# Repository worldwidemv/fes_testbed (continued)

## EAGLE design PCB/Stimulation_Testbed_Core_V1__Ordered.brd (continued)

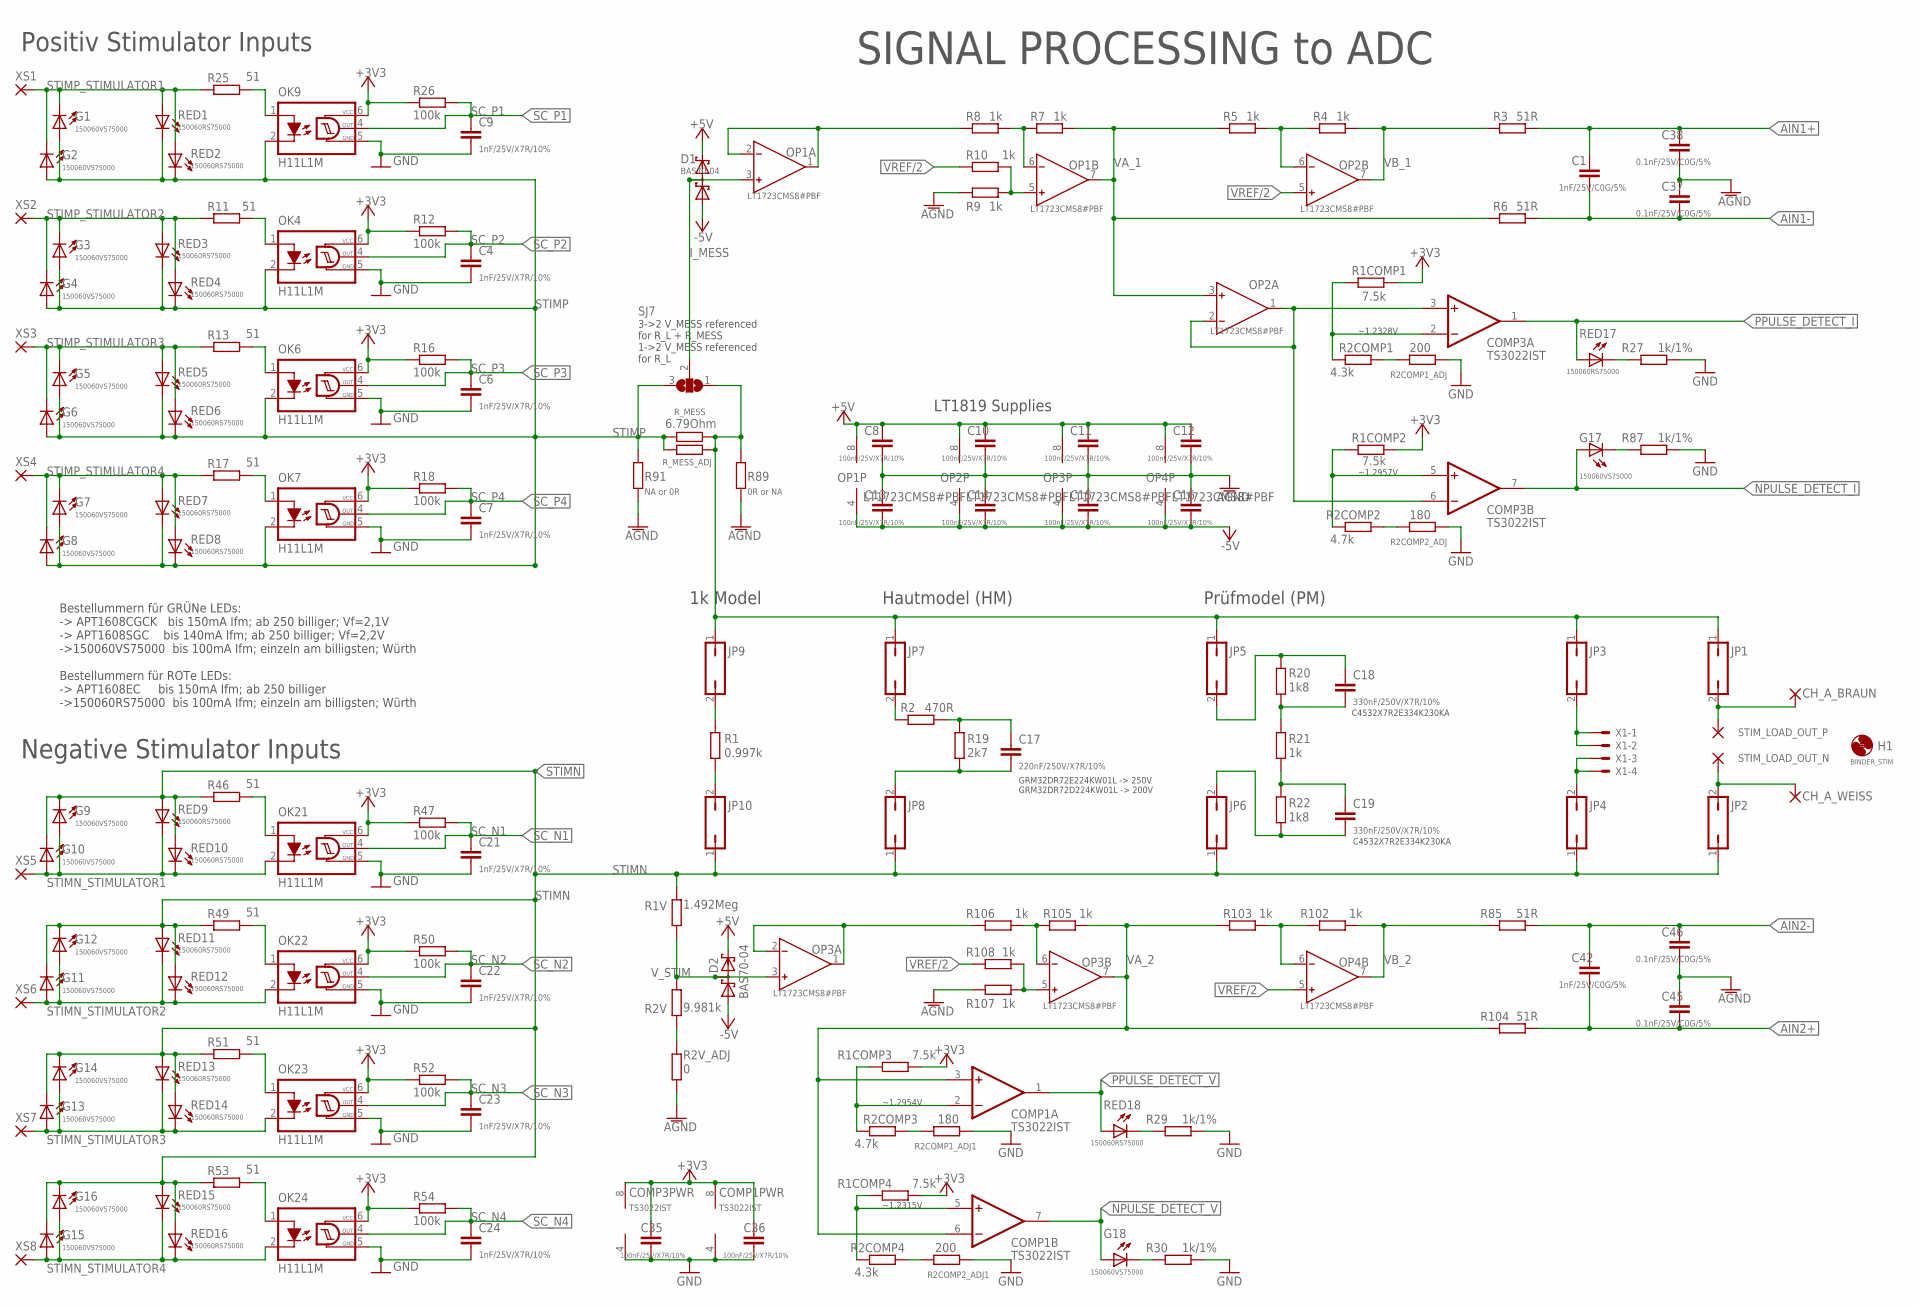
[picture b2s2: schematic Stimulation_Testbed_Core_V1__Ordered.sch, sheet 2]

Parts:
C1, C42: 1nF/25V/C0G/5%; C0603K
C4, C6, C7, C9, C21, C22, C23, C24: 1nF/25V/X7R/10%; C0603
C8, C10, C11, C12, C13, C14, C15, C16, C35, C36: 100nF/25V/X7R/10%; C0603K
C17: 220nF/250V/X7R/10%; C1210
C18, C19: 330nF/250V/X7R/10%; C1812
C37, C38, C45, C46: 0.1nF/25V/C0G/5%; C0603K
CH_A_BRAUN: 1,6/0,8
CH_A_WEISS: 1,6/0,8
COMP1, COMP3: TS3022IST; MSOP8
D1, D2: BAS70-04; SOT23
G1, G2, G3, G4, G5, G6, G7, G8, G9, G10, G11, G12, G13, G14, G15, G16, G17, G18: 150060VS75000; CHIPLED_0603
H1: BINDER_STIM; 5,5-PAD
JP1, JP2, JP3, JP4, JP5, JP6, JP7, JP8, JP9, JP10: JP1Q; JP1
OK4, OK6, OK7, OK9, OK21, OK22, OK23, OK24: H11L1M; DIL06
OP1, OP2, OP3, OP4: LT1723CMS8#PBF; MSOP8
R1: 0.997k; R1206
R1COMP1, R1COMP2, R1COMP3, R1COMP4: 7.5k; R0603
R1V: 1.492Meg; R1206
R2: 470R; R1206
R2COMP1, R2COMP4: 4.3k; R0603
R2COMP1_ADJ, R2COMP2_ADJ1: 200; R0603
R2COMP1_ADJ1, R2COMP2_ADJ: 180; R0603
R2COMP2, R2COMP3: 4.7k; R0603
R2V: 9.981k; R1206
R2V_ADJ: 0; R1206
R3, R6, R85, R104: 51R; R0603
R4, R5, R7, R8, R9, R10, R102, R103, R105, R106, R107, R108: 1k; R0603
R11, R13, R17, R25, R46, R49, R51, R53: 51; R0603
R12, R16, R18, R26, R47, R50, R52, R54: 100k; R0603
R19: 2k7; R1206
R20, R22: 1k8; R1206
R21: 1k; R1206
R27, R29, R30, R87: 1k/1%; R0603
R89: 0R or NA; R0603
R91: NA or 0R; R0603
RED1, RED2, RED3, RED4, RED5, RED6, RED7, RED8, RED9, RED10, RED11, RED12, RED13, RED14, RED15, RED16, RED17, RED18: 150060RS75000; CHIP-LED0603
R_MESS: 6.79Ohm; R1206
R_MESS_ADJ: R-EU_R1206; R1206
SJ7: SJ2W; SJ_2
STIM_LOAD_OUT_N: 3,81/1,4
STIM_LOAD_OUT_P: 3,81/1,4
X1: 22-23-2041
XS1, XS2, XS3, XS4, XS5, XS6, XS7, XS8: WIREPAD3,81/1,4; 3,81/1,4

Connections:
2XVREF: OP3.1 (OUT), OP3.2 (IN-), R106.2
2XVREF1: OP1.1 (OUT), OP1.2 (IN-), R8.2
+3V3: C35.1, C36.1, COMP1.8 (V+), COMP3.8 (V+), OK4.6 (VCC), OK6.6 (VCC), OK7.6 (VCC), OK9.6 (VCC), OK21.6 (VCC), OK22.6 (VCC), OK23.6 (VCC), OK24.6 (VCC), R1COMP1.1, R1COMP2.1, R1COMP3.1, R1COMP4.1, R12.1, R16.1, R18.1, R26.1, R47.1, R50.1, R52.1, R54.1; also elsewhere on the board
+5V: C8.1, C10.1, C11.1, C12.1, D1.2 (C2), D2.2 (C2), OP1.8 (V+), OP2.8 (V+), OP3.8 (V+), OP4.8 (V+); also elsewhere on the board
-5V: C13.2, C14.2, C15.2, C16.2, D1.1 (A1), D2.1 (A1), OP1.4 (V-), OP2.4 (V-), OP3.4 (V-), OP4.4 (V-); also elsewhere on the board
AGND: C8.2, C10.2, C11.2, C12.2, C13.1, C14.1, C15.1, C16.1, C37.2, C38.1, C45.2, C46.1, R2V_ADJ.2, R9.2, R89.2, R91.2, R107.2; also elsewhere on the board
AIN1+: C1.2, C38.2, R3.1; also elsewhere on the board
AIN1-: C1.1, C37.1, R6.2; also elsewhere on the board
AIN2+: C42.1, C45.1, R104.2; also elsewhere on the board
AIN2-: C42.2, C46.2, R85.1; also elsewhere on the board
GND: C4.2, C6.2, C7.2, C9.2, C21.2, C22.2, C23.2, C24.2, C35.2, C36.2, COMP1.4 (V-), COMP3.4 (V-), OK4.5 (GND), OK6.5 (GND), OK7.5 (GND), OK9.5 (GND), OK21.5 (GND), OK22.5 (GND), OK23.5 (GND), OK24.5 (GND), R2COMP1_ADJ.1, R2COMP1_ADJ1.1, R2COMP2_ADJ.1, R2COMP2_ADJ1.1, R27.1, R29.1, R30.1, R87.1; also elsewhere on the board
I_MESS: D1.3 (C1A2), OP1.3 (IN+), SJ7.2
unnamed: OK4.1 (A), R11.1
unnamed: R2COMP2.2, R2COMP2_ADJ.2
unnamed: R29.2, RED18.C
unnamed: G18.C, R30.2
unnamed: COMP1.2 (-IN), R1COMP3.2, R2COMP3.1
unnamed: COMP1.5 (+IN), R1COMP4.2, R2COMP4.1
unnamed: G17.C, R87.2
unnamed: OP1.5 (IN+), R9.1, R10.1
unnamed: R2COMP1_ADJ1.2, R2COMP3.2
unnamed: R2COMP2_ADJ1.2, R2COMP4.2
unnamed: OK6.1 (A), R13.1
unnamed: OK7.1 (A), R17.1
unnamed: OK9.1 (A), R25.1
unnamed: OP1.6 (IN-), R7.2, R8.1
unnamed: OP2.6 (IN-), R4.2, R5.1
unnamed: COMP3.3 (+IN), COMP3.6 (-IN), OP2.1 (OUT), OP2.2 (IN-)
unnamed: OK21.1 (A), R46.1
unnamed: COMP3.2 (-IN), R1COMP1.2, R2COMP1.1
unnamed: CH_A_WEISS.1, JP2.2, STIM_LOAD_OUT_N.1
unnamed: OK22.1 (A), R49.1
unnamed: OK23.1 (A), R51.1
unnamed: OK24.1 (A), R53.1
unnamed: R2V.1, R2V_ADJ.1
unnamed: OP3.5 (IN+), R107.1, R108.1
unnamed: CH_A_BRAUN.1, JP1.2, STIM_LOAD_OUT_P.1
unnamed: JP3.2, X1.1, X1.2
unnamed: JP9.2, R1.1
unnamed: JP4.2, X1.3, X1.4
unnamed: JP10.2, R1.2
unnamed: JP7.2, R2.2
unnamed: OP3.6 (IN-), R105.2, R106.1
unnamed: C17.1, JP8.2, R19.2
unnamed: C19.2, R21.2, R22.1
unnamed: C19.1, JP6.2, R22.2
unnamed: C18.2, JP5.2, R20.1
unnamed: C18.1, R20.2, R21.1
unnamed: OP4.6 (IN-), R102.2, R103.1
unnamed: C17.2, R2.1, R19.1
unnamed: R27.2, RED17.C
unnamed: COMP3.5 (+IN), R1COMP2.2, R2COMP2.1
unnamed: R2COMP1.2, R2COMP1_ADJ.2
NPULSE_DETECT_I: COMP3.7 (OUT), G17.A; also elsewhere on the board
NPULSE_DETECT_V: COMP1.7 (OUT), G18.A; also elsewhere on the board
PPULSE_DETECT_I: COMP3.1 (OUT), RED17.A; also elsewhere on the board
PPULSE_DETECT_V: COMP1.1 (OUT), RED18.A; also elsewhere on the board
SC_N1: C21.1, OK21.4 (OUT), R47.2; also elsewhere on the board
SC_N2: C22.1, OK22.4 (OUT), R50.2; also elsewhere on the board
SC_N3: C23.1, OK23.4 (OUT), R52.2; also elsewhere on the board
SC_N4: C24.1, OK24.4 (OUT), R54.2; also elsewhere on the board
SC_P1: C9.1, OK9.4 (OUT), R26.2; also elsewhere on the board
SC_P2: C4.1, OK4.4 (OUT), R12.2; also elsewhere on the board
SC_P3: C6.1, OK6.4 (OUT), R16.2; also elsewhere on the board
SC_P4: C7.1, OK7.4 (OUT), R18.2; also elsewhere on the board
STIMN: G9.C, G10.C, G11.C, G12.C, G13.C, G14.C, G15.C, G16.C, JP2.1, JP4.1, JP6.1, JP8.1, JP10.1, R1V.2, R46.2, R49.2, R51.2, R53.2, RED9.A, RED10.A, RED11.A, RED12.A, RED13.A, RED14.A, RED15.A, RED16.A; also elsewhere on the board
STIMN_STIMULATOR1: G9.A, G10.A, OK21.2 (C), RED9.C, RED10.C, XS5.1
STIMN_STIMULATOR2: G11.A, G12.A, OK22.2 (C), RED11.C, RED12.C, XS6.1
STIMN_STIMULATOR3: G13.A, G14.A, OK23.2 (C), RED13.C, RED14.C, XS7.1
STIMN_STIMULATOR4: G15.A, G16.A, OK24.2 (C), RED15.C, RED16.C, XS8.1
STIMP: G1.A, G2.A, G3.A, G4.A, G5.A, G6.A, G7.A, G8.A, OK4.2 (C), OK6.2 (C), OK7.2 (C), OK9.2 (C), R91.1, RED1.C, RED2.C, RED3.C, RED4.C, RED5.C, RED6.C, RED7.C, RED8.C, R_MESS.2, R_MESS_ADJ.1, SJ7.3; also elsewhere on the board
STIMP_MODEL: JP1.1, JP3.1, JP5.1, JP7.1, JP9.1, R89.1, R_MESS.1, R_MESS_ADJ.2, SJ7.1
STIMP_STIMULATOR1: G1.C, G2.C, R25.2, RED1.A, RED2.A, XS1.1
STIMP_STIMULATOR2: G3.C, G4.C, R11.2, RED3.A, RED4.A, XS2.1
STIMP_STIMULATOR3: G5.C, G6.C, R13.2, RED5.A, RED6.A, XS3.1
STIMP_STIMULATOR4: G7.C, G8.C, R17.2, RED7.A, RED8.A, XS4.1
VA_1: OP1.7 (OUT), OP2.3 (IN+), R5.2, R6.1, R7.1
VA_2: COMP1.3 (+IN), COMP1.6 (-IN), OP3.7 (OUT), R103.2, R104.1, R105.1
VB_1: OP2.7 (OUT), R3.2, R4.1
VB_2: OP4.7 (OUT), R85.2, R102.1
VREF/2: OP2.5 (IN+), OP4.5 (IN+), R10.2, R108.2; also elsewhere on the board
V_STIM: D2.3 (C1A2), OP3.3 (IN+), R1V.1, R2V.2

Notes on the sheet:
LT1819 Supplies
1k Model
Hautmodel (HM)
Prüfmodel (PM)
SIGNAL PROCESSING to ADC
3->2 V_MESS referenced for R_L + R_MESS 1->2 V_MESS referenced for R_L
Positiv Stimulator Inputs
Negative Stimulator Inputs
C4532X7R2E334K230KA
GRM32DR72E224KW01L -> 250V GRM32DR72D224KW01L -> 200V
Bestellummern für GRÜNe LEDs: -> APT1608CGCK bis 150mA Ifm; ab 250 billiger; Vf=2,1V -> APT1608SGC bis 140mA Ifm; ab 250 billiger; Vf=2,2V ->150060VS75000 bis 100mA Ifm; einzeln am billigsten; Würth Bestellummern für ROTe LEDs: -> APT1608EC bis 150mA Ifm; ab 250 billiger ->150060RS75000 bis 100mA I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
~1.2328V
~1.2957V
~1.2954V
~1.2315V

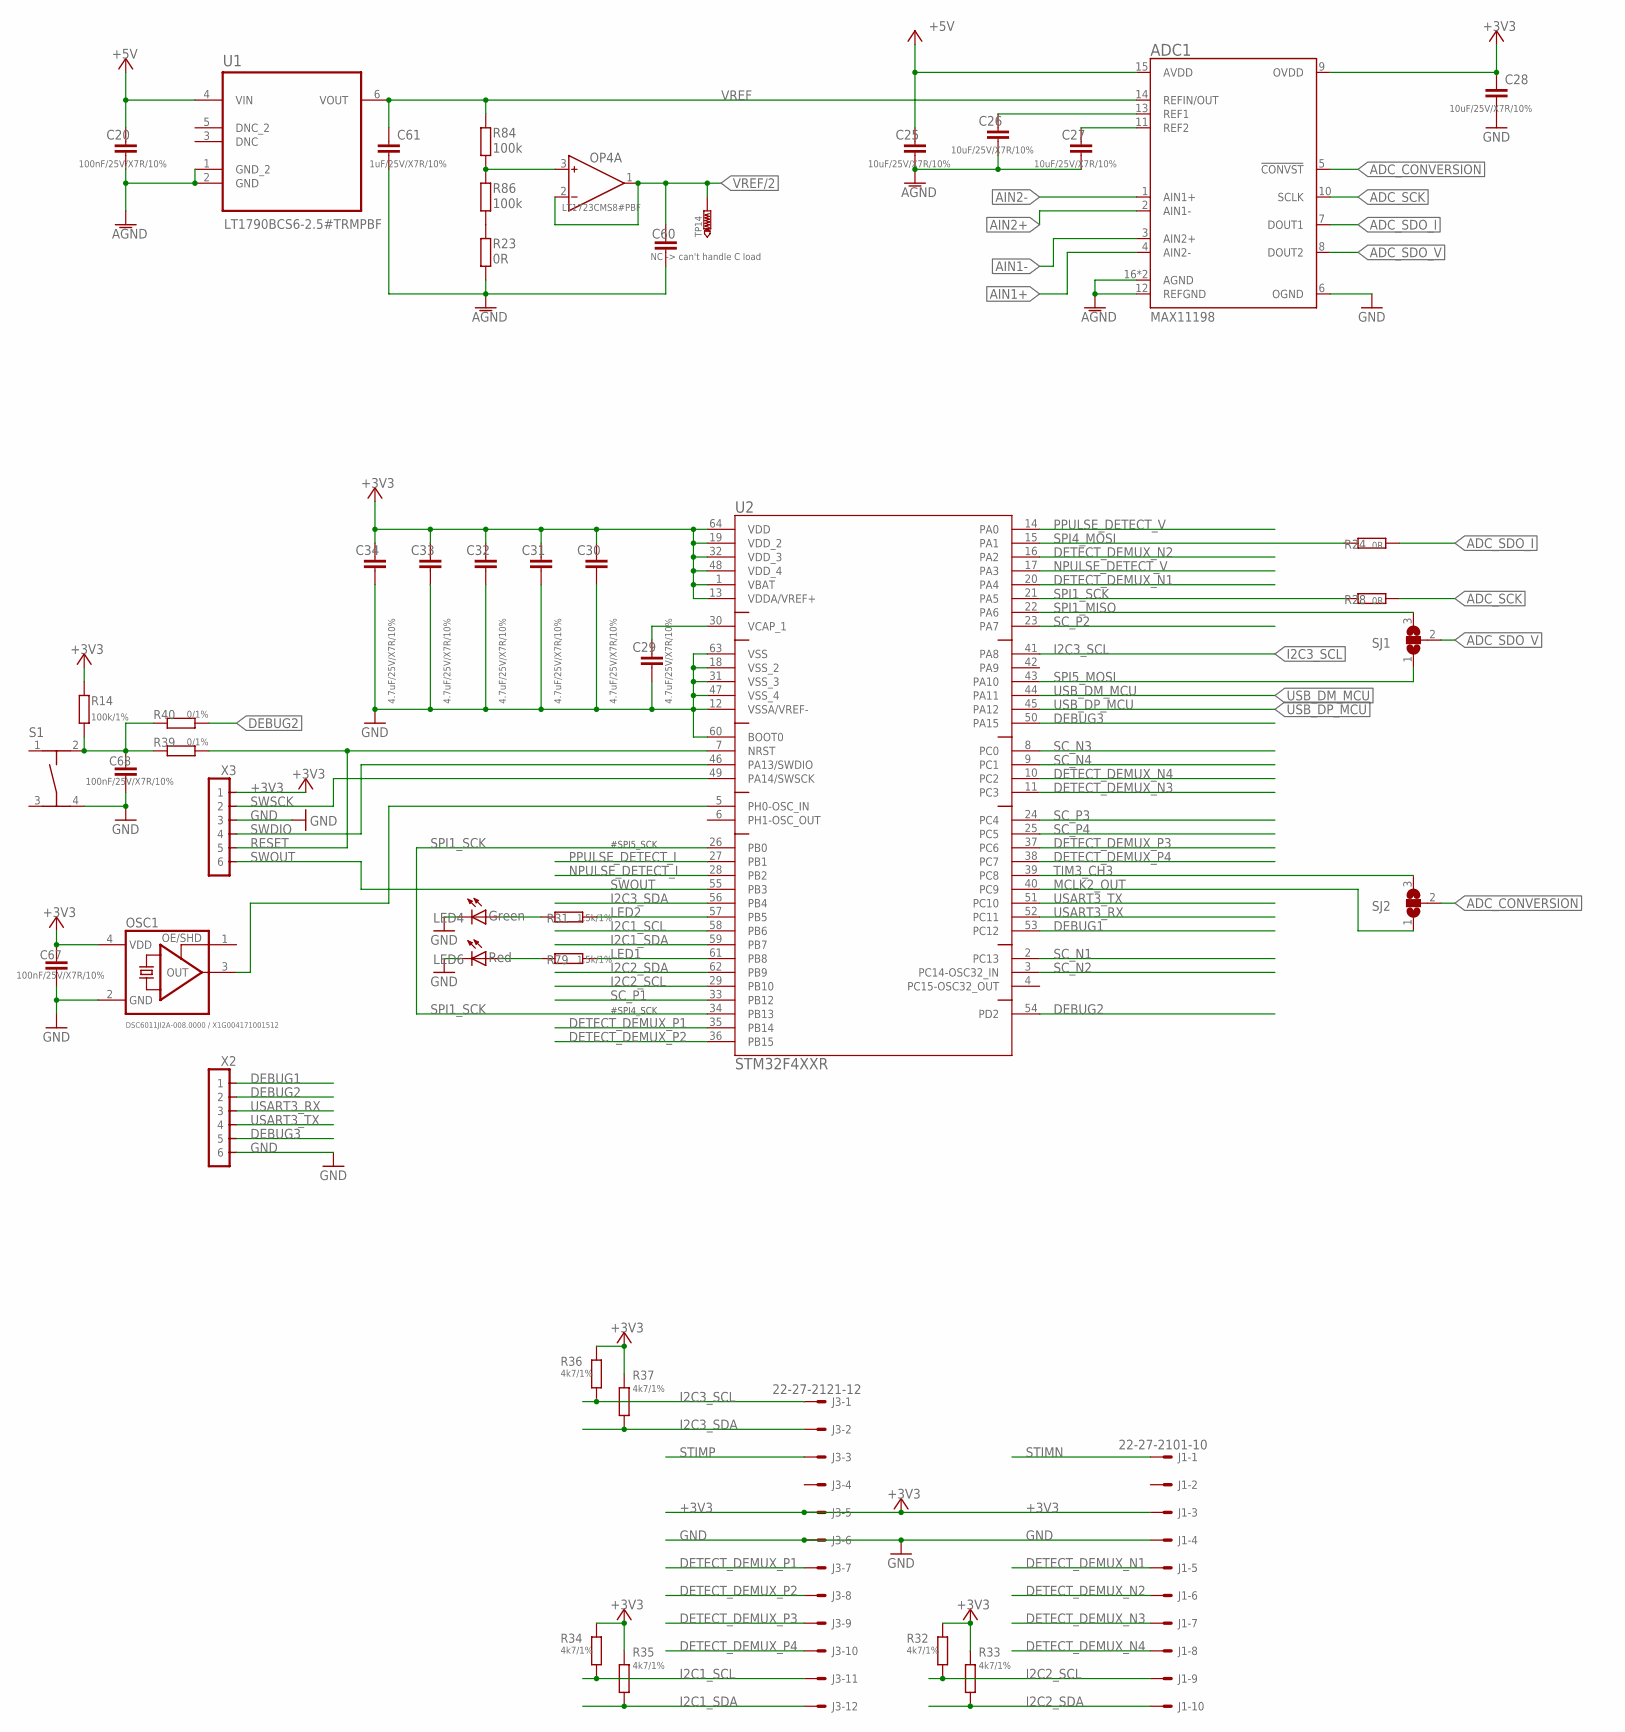
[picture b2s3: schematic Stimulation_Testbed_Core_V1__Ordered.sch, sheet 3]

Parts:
ADC1: MAX11198; T1623CN+1
C20, C67, C68: 100nF/25V/X7R/10%; C0603K
C25, C26, C27, C28: 10uF/25V/X7R/10%; C0603K
C29, C30, C31, C32, C33, C34: 4.7uF/25V/X7R/10%; C0603K
C60: NC -> can't handle C load; C0603K
C61: 1uF/25V/X7R/10%; C0603K
J1: 22-27-2101-10; 6410-10
J3: 22-27-2121-12; 6410-12
LED4: Green; CHIPLED_0603
LED6: Red; CHIPLED_0603
OP4: LT1723CMS8#PBF; MSOP8
OSC1: DSC6011JI2A-008.0000 / X1G004171001512; OSC_2.5X2
R14: 100k/1%; R0603
R23, R24, R28: 0R; R0603
R31, R79: 1.5k/1%; R0603
R32, R33, R34, R35, R36, R37: 4k7/1%; R0603
R39, R40: 0/1%; R0603
R84, R86: 100k; R0603
S1: TASTERSMD; TAST_SMD
SJ1, SJ2: SJ2W; SJ_2
TP14: TESTPOINT_TH; TP1-09
U1: LT1790BCS6-2.5#TRMPBF; SOT95P280X100-6N
U2: STM32F4XXR; LQFP64-10X10MM
X2, X3: PINHD-1X66X1.27; 1.27_1X06_S

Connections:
+3V3: ADC1.9 (OVDD), C28.1, C30.1, C31.1, C32.1, C33.1, C34.1, C67.1, J1.3, J3.5, OSC1.4 (VDD), R14.2, R32.1, R33.1, R34.1, R35.1, R36.1, R37.1, U2.1 (VBAT), U2.13 (VDDA/VREF+), U2.19 (VDD_2), U2.32 (VDD_3), U2.48 (VDD_4), U2.64 (VDD), X3.P1 (1); also elsewhere on the board
+5V: ADC1.15 (AVDD), C20.1, C25.1, U1.4 (VIN); also elsewhere on the board
ADC_CONVERSION: ADC1.5 (!CONVST!), SJ2.2
ADC_SCK: ADC1.10 (SCLK), R28.2
ADC_SDO_I: ADC1.7 (DOUT1), R24.2
ADC_SDO_V: ADC1.8 (DOUT2), SJ1.2
AGND: ADC1.12 (REFGND), ADC1.16 (AGND), ADC1.EXP (AGND), C20.2, C25.2, C26.2, C27.2, C60.2, C61.2, R23.2, U1.1 (GND_2), U1.2 (GND); also elsewhere on the board
AIN1+: ADC1.4 (AIN2-); also elsewhere on the board
AIN1-: ADC1.3 (AIN2+); also elsewhere on the board
AIN2+: ADC1.2 (AIN1-); also elsewhere on the board
AIN2-: ADC1.1 (AIN1+); also elsewhere on the board
DEBUG1: U2.53 (PC12), X2.P1 (1)
DEBUG2: R40.1, U2.54 (PD2), X2.P2 (2)
DEBUG3: U2.50 (PA15), X2.P5 (5)
DETECT_DEMUX_N1: J1.5, U2.20 (PA4)
DETECT_DEMUX_N2: J1.6, U2.16 (PA2)
DETECT_DEMUX_N3: J1.7, U2.11 (PC3)
DETECT_DEMUX_N4: J1.8, U2.10 (PC2)
DETECT_DEMUX_P1: J3.7, U2.35 (PB14)
DETECT_DEMUX_P2: J3.8, U2.36 (PB15)
DETECT_DEMUX_P3: J3.9, U2.37 (PC6)
DETECT_DEMUX_P4: J3.10, U2.38 (PC7)
GND: ADC1.6 (OGND), C28.2, C29.2, C30.2, C31.2, C32.2, C33.2, C34.2, C67.2, C68.2, J1.4, J3.6, LED4.C, LED6.C, OSC1.2 (GND), S1.4, U2.12 (VSSA/VREF-), U2.18 (VSS_2), U2.31 (VSS_3), U2.47 (VSS_4), U2.60 (BOOT0), U2.63 (VSS), X2.P6 (6), X3.P3 (3); also elsewhere on the board
I2C1_SCL: J3.11, R34.2, U2.58 (PB6)
I2C1_SDA: J3.12, R35.2, U2.59 (PB7)
I2C2_SCL: J1.9, R32.2, U2.29 (PB10)
I2C2_SDA: J1.10, R33.2, U2.62 (PB9)
I2C3_SCL: J3.1, R36.2, U2.41 (PA8)
I2C3_SDA: J3.2, R37.2, U2.56 (PB4)
LED1: R79.1, U2.61 (PB8)
LED2: R31.1, U2.57 (PB5)
MCLK2_OUT: SJ2.1, U2.40 (PC9)
unnamed: LED4.A, R31.2
unnamed: C29.1, U2.30 (VCAP_1)
unnamed: R23.1, R86.1
unnamed: C68.1, R14.1, R39.2, R40.2, S1.2
unnamed: ADC1.11 (REF2), C27.1
unnamed: ADC1.13 (REF1), C26.1
unnamed: OP4.3 (IN+), R84.2, R86.2
unnamed: OSC1.3 (OUT), U2.5 (PH0-OSC_IN)
unnamed: LED6.A, R79.2
NPULSE_DETECT_I: U2.28 (PB2); also elsewhere on the board
NPULSE_DETECT_V: U2.17 (PA3); also elsewhere on the board
PPULSE_DETECT_I: U2.27 (PB1); also elsewhere on the board
PPULSE_DETECT_V: U2.14 (PA0); also elsewhere on the board
RESET: R39.1, U2.7 (NRST), X3.P5 (5)
SC_N1: U2.2 (PC13); also elsewhere on the board
SC_N2: U2.3 (PC14-OSC32_IN); also elsewhere on the board
SC_N3: U2.8 (PC0); also elsewhere on the board
SC_N4: U2.9 (PC1); also elsewhere on the board
SC_P1: U2.33 (PB12); also elsewhere on the board
SC_P2: U2.23 (PA7); also elsewhere on the board
SC_P3: U2.24 (PC4); also elsewhere on the board
SC_P4: U2.25 (PC5); also elsewhere on the board
SPI1_MISO: SJ1.3, U2.22 (PA6)
SPI1_SCK: R28.1, U2.21 (PA5), U2.26 (PB0), U2.34 (PB13)
SPI4_MOSI: R24.1, U2.15 (PA1)
SPI5_MOSI: SJ1.1, U2.43 (PA10)
STIMN: J1.1; also elsewhere on the board
STIMP: J3.3; also elsewhere on the board
SWDIO: U2.46 (PA13/SWDIO), X3.P4 (4)
SWOUT: U2.55 (PB3), X3.P6 (6)
SWSCK: U2.49 (PA14/SWSCK), X3.P2 (2)
TIM3_CH3: SJ2.3, U2.39 (PC8)
USART3_RX: U2.52 (PC11), X2.P3 (3)
USART3_TX: U2.51 (PC10), X2.P4 (4)
USB_DM_MCU: U2.44 (PA11); also elsewhere on the board
USB_DP_MCU: U2.45 (PA12); also elsewhere on the board
VREF: ADC1.14 (REFIN/OUT), C61.1, R84.1, U1.6 (VOUT)
VREF/2: C60.1, OP4.1 (OUT), OP4.2 (IN-), TP14.TP; also elsewhere on the board

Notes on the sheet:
#SPI5_SCK
#SPI4_SCK

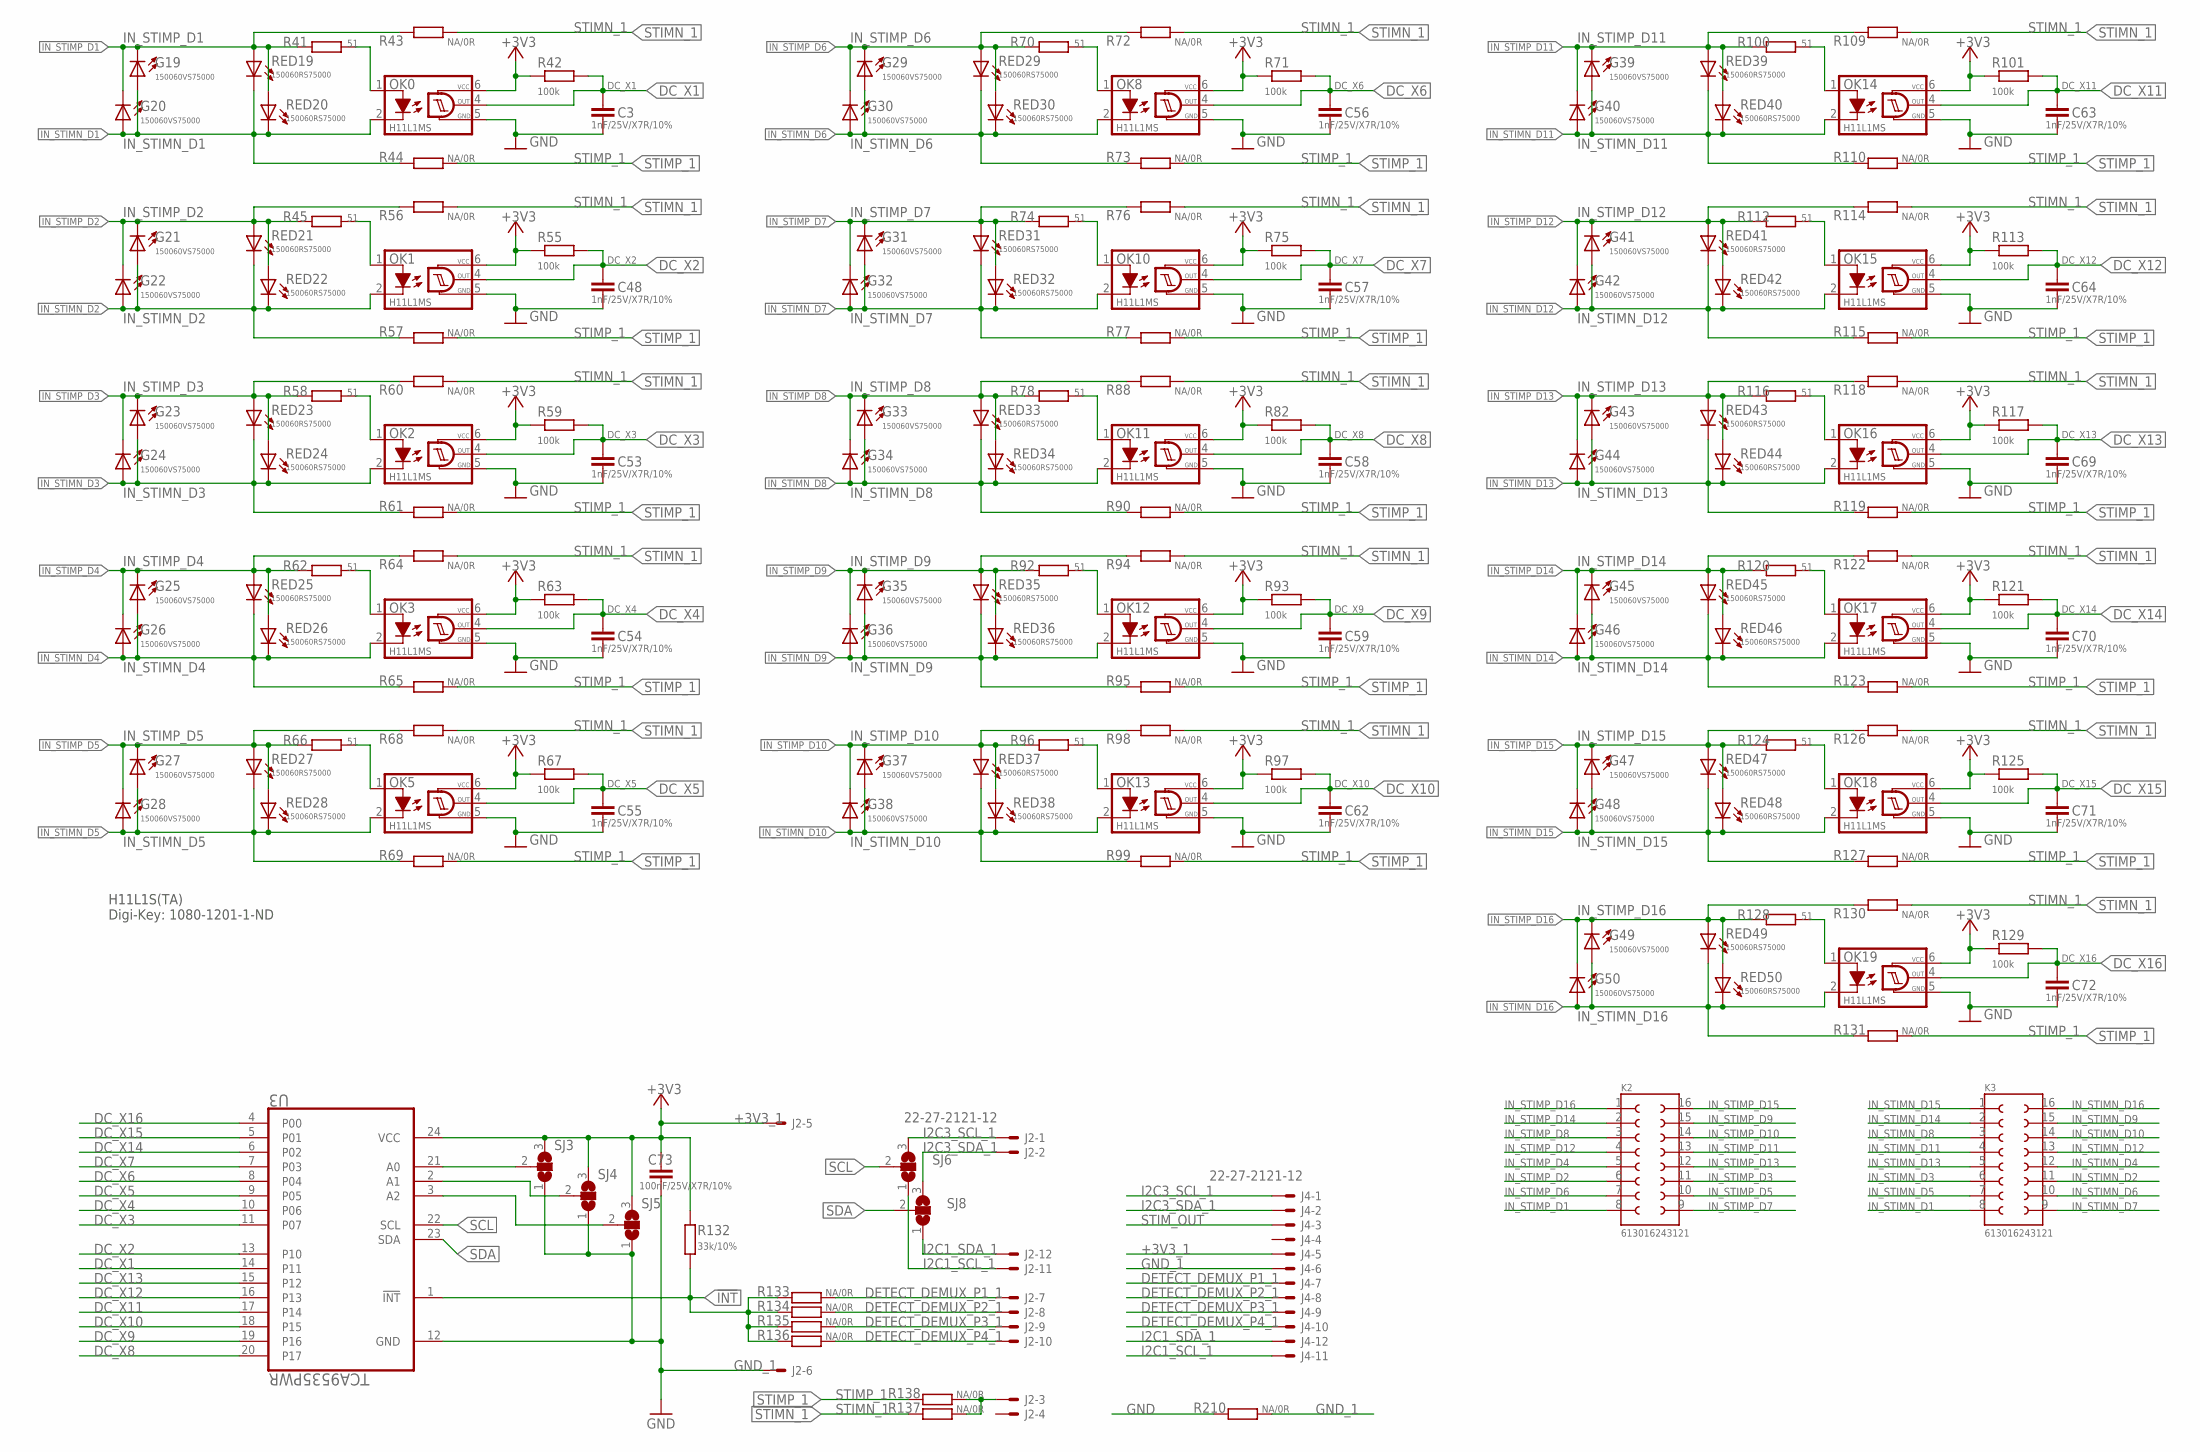
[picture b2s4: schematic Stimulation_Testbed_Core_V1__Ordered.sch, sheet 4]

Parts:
C3, C48, C53, C54, C55, C56, C57, C58, C59, C62, C63, C64, C69, C70, C71, C72: 1nF/25V/X7R/10%; C0603
C73: 100nF/25V/X7R/10%; C0603K
G19, G20, G21, G22, G23, G24, G25, G26, G27, G28, G29, G30, G31, G32, G33, G34, G35, G36, G37, G38, G39, G40, G41, G42, G43, G44, G45, G46, G47, G48, G49, G50: 150060VS75000; CHIPLED_0603
J2, J4: 22-27-2121-12; 6410-12
K2, K3: 613016243121
OK0, OK1, OK2, OK3, OK5, OK8, OK10, OK11, OK12, OK13, OK14, OK15, OK16, OK17, OK18, OK19: H11L1MS; DIL6-SMD
R41, R45, R58, R62, R66, R70, R74, R78, R92, R96, R100, R112, R116, R120, R124, R128: 51; R0603
R42, R55, R59, R63, R67, R71, R75, R82, R93, R97, R101, R113, R117, R121, R125, R129: 100k; R0603
R43, R44, R56, R57, R60, R61, R64, R65, R68, R69, R72, R73, R76, R77, R88, R90, R94, R95, R98, R99, R109, R110, R114, R115, R118, R119, R122, R123, R126, R127, R130, R131, R133, R134, R135, R136, R137, R138: NA/0R; R0603
R132: 33k/10%; R0603
R210: NA/0R; R6332
RED19, RED20, RED21, RED22, RED23, RED24, RED25, RED26, RED27, RED28, RED29, RED30, RED31, RED32, RED33, RED34, RED35, RED36, RED37, RED38, RED39, RED40, RED41, RED42, RED43, RED44, RED45, RED46, RED47, RED48, RED49, RED50: 150060RS75000; CHIP-LED0603
SJ3, SJ4, SJ5, SJ6, SJ8: SJ2W; SJ_2
U3: TCA9535PWR; SOP65P640X120-24N

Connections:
!INT: R132.1, R133.2, R134.2, R135.2, R136.2, U3.1 (!INT)
+3V3_1: C73.1, J2.5, J4.5, OK0.6 (VCC), OK1.6 (VCC), OK2.6 (VCC), OK3.6 (VCC), OK5.6 (VCC), OK8.6 (VCC), OK10.6 (VCC), OK11.6 (VCC), OK12.6 (VCC), OK13.6 (VCC), OK14.6 (VCC), OK15.6 (VCC), OK16.6 (VCC), OK17.6 (VCC), OK18.6 (VCC), OK19.6 (VCC), R42.1, R55.1, R59.1, R63.1, R67.1, R71.1, R75.1, R82.1, R93.1, R97.1, R101.1, R113.1, R117.1, R121.1, R125.1, R129.1, R132.2, SJ3.3, SJ4.3, SJ5.3, U3.24 (VCC)
DC_X1: C3.1, OK0.4 (OUT), R42.2, U3.14 (P11)
DC_X2: C48.1, OK1.4 (OUT), R55.2, U3.13 (P10)
DC_X3: C53.1, OK2.4 (OUT), R59.2, U3.11 (P07)
DC_X4: C54.1, OK3.4 (OUT), R63.2, U3.10 (P06)
DC_X5: C55.1, OK5.4 (OUT), R67.2, U3.9 (P05)
DC_X6: C56.1, OK8.4 (OUT), R71.2, U3.8 (P04)
DC_X7: C57.1, OK10.4 (OUT), R75.2, U3.7 (P03)
DC_X8: C58.1, OK11.4 (OUT), R82.2, U3.20 (P17)
DC_X9: C59.1, OK12.4 (OUT), R93.2, U3.19 (P16)
DC_X10: C62.1, OK13.4 (OUT), R97.2, U3.18 (P15)
DC_X11: C63.1, OK14.4 (OUT), R101.2, U3.17 (P14)
DC_X12: C64.1, OK15.4 (OUT), R113.2, U3.16 (P13)
DC_X13: C69.1, OK16.4 (OUT), R117.2, U3.15 (P12)
DC_X14: C70.1, OK17.4 (OUT), R121.2, U3.6 (P02)
DC_X15: C71.1, OK18.4 (OUT), R125.2, U3.5 (P01)
DC_X16: C72.1, OK19.4 (OUT), R129.2, U3.4 (P00)
DETECT_DEMUX_P1_1: J2.7, J4.7, R133.1
DETECT_DEMUX_P2_1: J2.8, J4.8, R134.1
DETECT_DEMUX_P3_1: J2.9, J4.9, R135.1
DETECT_DEMUX_P4_1: J2.10, J4.10, R136.1
GND: R210.2; also elsewhere on the board
GND_1: C3.2, C48.2, C53.2, C54.2, C55.2, C56.2, C57.2, C58.2, C59.2, C62.2, C63.2, C64.2, C69.2, C70.2, C71.2, C72.2, C73.2, J2.6, J4.6, OK0.5 (GND), OK1.5 (GND), OK2.5 (GND), OK3.5 (GND), OK5.5 (GND), OK8.5 (GND), OK10.5 (GND), OK11.5 (GND), OK12.5 (GND), OK13.5 (GND), OK14.5 (GND), OK15.5 (GND), OK16.5 (GND), OK17.5 (GND), OK18.5 (GND), OK19.5 (GND), R210.1, SJ3.1, SJ4.1, SJ5.1, U3.12 (GND); also elsewhere on the board
I2C1_SCL_1: J2.11, J4.11, SJ6.1
I2C1_SDA_1: J2.12, J4.12, SJ8.1
I2C3_SCL_1: J2.1, J4.1, SJ6.3
I2C3_SDA_1: J2.2, J4.2, SJ8.3
IN_STIMN_D1: G19.A, G20.A, K3.8, OK0.2 (C), R44.2, RED19.C, RED20.C
IN_STIMN_D2: G21.A, G22.A, K3.11, OK1.2 (C), R57.2, RED21.C, RED22.C
IN_STIMN_D3: G23.A, G24.A, K3.6, OK2.2 (C), R61.2, RED23.C, RED24.C
IN_STIMN_D4: G25.A, G26.A, K3.12, OK3.2 (C), R65.2, RED25.C, RED26.C
IN_STIMN_D5: G27.A, G28.A, K3.7, OK5.2 (C), R69.2, RED27.C, RED28.C
IN_STIMN_D6: G29.A, G30.A, K3.10, OK8.2 (C), R73.2, RED29.C, RED30.C
IN_STIMN_D7: G31.A, G32.A, K3.9, OK10.2 (C), R77.2, RED31.C, RED32.C
IN_STIMN_D8: G33.A, G34.A, K3.3, OK11.2 (C), R90.2, RED33.C, RED34.C
IN_STIMN_D9: G35.A, G36.A, K3.15, OK12.2 (C), R95.2, RED35.C, RED36.C
IN_STIMN_D10: G37.A, G38.A, K3.14, OK13.2 (C), R99.2, RED37.C, RED38.C
IN_STIMN_D11: G39.A, G40.A, K3.4, OK14.2 (C), R110.2, RED39.C, RED40.C
IN_STIMN_D12: G41.A, G42.A, K3.13, OK15.2 (C), R115.2, RED41.C, RED42.C
IN_STIMN_D13: G43.A, G44.A, K3.5, OK16.2 (C), R119.2, RED43.C, RED44.C
IN_STIMN_D14: G45.A, G46.A, K3.2, OK17.2 (C), R123.2, RED45.C, RED46.C
IN_STIMN_D15: G47.A, G48.A, K3.1, OK18.2 (C), R127.2, RED47.C, RED48.C
IN_STIMN_D16: G49.A, G50.A, K3.16, OK19.2 (C), R131.2, RED49.C, RED50.C
IN_STIMP_D1: G19.C, G20.C, K2.8, R41.2, R43.2, RED19.A, RED20.A
IN_STIMP_D2: G21.C, G22.C, K2.6, R45.2, R56.2, RED21.A, RED22.A
IN_STIMP_D3: G23.C, G24.C, K2.11, R58.2, R60.2, RED23.A, RED24.A
IN_STIMP_D4: G25.C, G26.C, K2.5, R62.2, R64.2, RED25.A, RED26.A
IN_STIMP_D5: G27.C, G28.C, K2.10, R66.2, R68.2, RED27.A, RED28.A
IN_STIMP_D6: G29.C, G30.C, K2.7, R70.2, R72.2, RED29.A, RED30.A
IN_STIMP_D7: G31.C, G32.C, K2.9, R74.2, R76.2, RED31.A, RED32.A
IN_STIMP_D8: G33.C, G34.C, K2.3, R78.2, R88.2, RED33.A, RED34.A
IN_STIMP_D9: G35.C, G36.C, K2.15, R92.2, R94.2, RED35.A, RED36.A
IN_STIMP_D10: G37.C, G38.C, K2.14, R96.2, R98.2, RED37.A, RED38.A
IN_STIMP_D11: G39.C, G40.C, K2.13, R100.2, R109.2, RED39.A, RED40.A
IN_STIMP_D12: G41.C, G42.C, K2.4, R112.2, R114.2, RED41.A, RED42.A
IN_STIMP_D13: G43.C, G44.C, K2.12, R116.2, R118.2, RED43.A, RED44.A
IN_STIMP_D14: G45.C, G46.C, K2.2, R120.2, R122.2, RED45.A, RED46.A
IN_STIMP_D15: G47.C, G48.C, K2.16, R124.2, R126.2, RED47.A, RED48.A
IN_STIMP_D16: G49.C, G50.C, K2.1, R128.2, R130.2, RED49.A, RED50.A
unnamed: OK1.1 (A), R45.1
unnamed: OK0.1 (A), R41.1
unnamed: OK2.1 (A), R58.1
unnamed: OK3.1 (A), R62.1
unnamed: OK5.1 (A), R66.1
unnamed: OK8.1 (A), R70.1
unnamed: OK10.1 (A), R74.1
unnamed: OK11.1 (A), R78.1
unnamed: OK13.1 (A), R96.1
unnamed: OK12.1 (A), R92.1
unnamed: OK14.1 (A), R100.1
unnamed: OK15.1 (A), R112.1
unnamed: OK16.1 (A), R116.1
unnamed: OK17.1 (A), R120.1
unnamed: OK18.1 (A), R124.1
unnamed: OK19.1 (A), R128.1
unnamed: SJ3.2, U3.21 (A0)
unnamed: SJ4.2, U3.2 (A1)
unnamed: SJ5.2, U3.3 (A2)
SCL: SJ6.2, U3.22 (SCL)
SDA: SJ8.2, U3.23 (SDA)
STIMN_1: R43.1, R56.1, R60.1, R64.1, R68.1, R72.1, R76.1, R88.1, R94.1, R98.1, R109.1, R114.1, R118.1, R122.1, R126.1, R130.1, R137.2
STIMP_1: R44.1, R57.1, R61.1, R65.1, R69.1, R73.1, R77.1, R90.1, R95.1, R99.1, R110.1, R115.1, R119.1, R123.1, R127.1, R131.1, R138.2
STIM_OUT: J2.3, J4.3, R137.1, R138.1

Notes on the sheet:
H11L1S(TA) Digi-Key: 1080-1201-1-ND
